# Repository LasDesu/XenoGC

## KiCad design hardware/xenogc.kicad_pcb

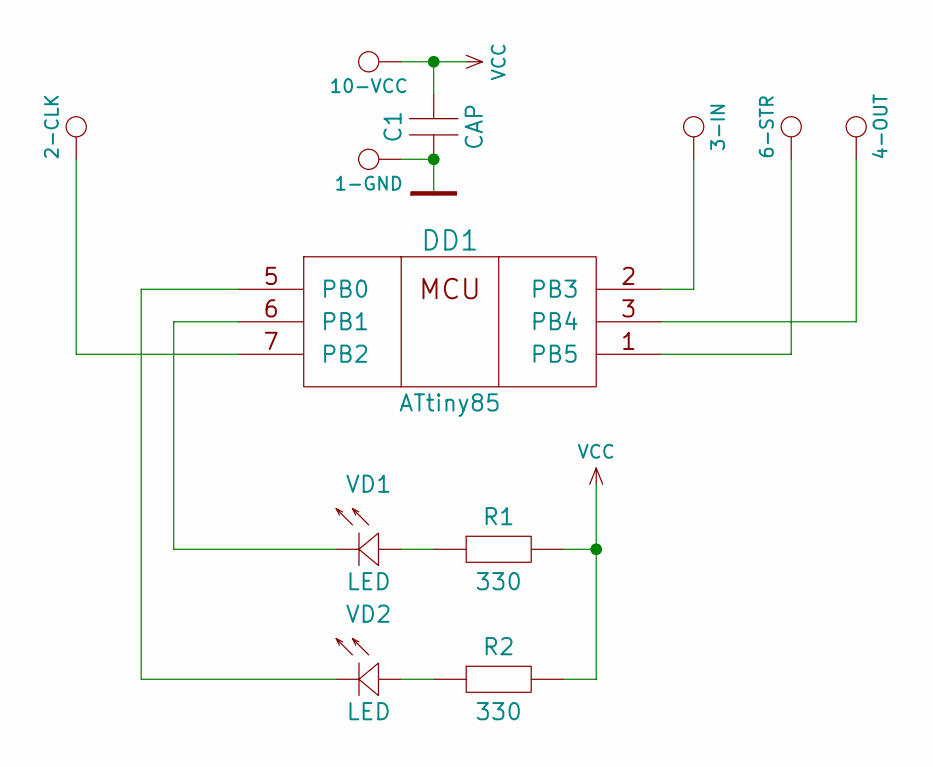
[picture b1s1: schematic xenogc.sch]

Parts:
C1: CAP; C_0805_HandSoldering
DD1: ATtiny85; SOIJ-8_5.3x5.3mm_Pitch1.27mm
P1: 10-VCC; Measurement_Point_Square-SMD-Pad_Small
P2: 1-GND; Measurement_Point_Square-SMD-Pad_Small
P3: 3-IN; Measurement_Point_Square-SMD-Pad_Small
P4: 4-OUT; Measurement_Point_Square-SMD-Pad_Small
P5: 2-CLK; Measurement_Point_Square-SMD-Pad_Small
P6: 6-STR; Measurement_Point_Square-SMD-Pad_Small
R1, R2: 330; R_0805_HandSoldering
VD1, VD2: LED; LED_0805_HandSoldering

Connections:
GND: C1.1, DD1.4 (GND), P2.1
unnamed: DD1.1 (PB5), P6.1
unnamed: DD1.2 (PB3), P3.1
unnamed: DD1.3 (PB4), P4.1
unnamed: DD1.5 (PB0), VD2.1
unnamed: DD1.6 (PB1), VD1.1
unnamed: DD1.7 (PB2), P5.1
unnamed: R1.1, VD1.2
unnamed: R2.1, VD2.2
VCC: C1.2, DD1.8 (VCC), P1.1, R1.2, R2.2

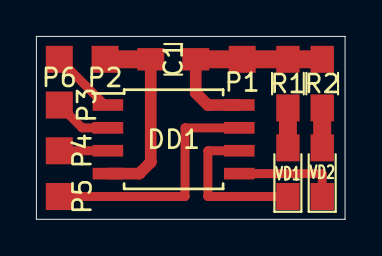
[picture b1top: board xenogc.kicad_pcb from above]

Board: 2 copper layers, 17.1 x 10.2 mm, 12 parts (0 on the bottom side), 10 nets.

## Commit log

2020-04-22 Fixes for newer toolchains; ATtiny85 support
2020-04-22 Cleanup binary files
2020-04-22 KiCad project for XenoGC on ATtiny85
2020-04-22 Disable verbose output
2020-04-22 More binary cleanup
